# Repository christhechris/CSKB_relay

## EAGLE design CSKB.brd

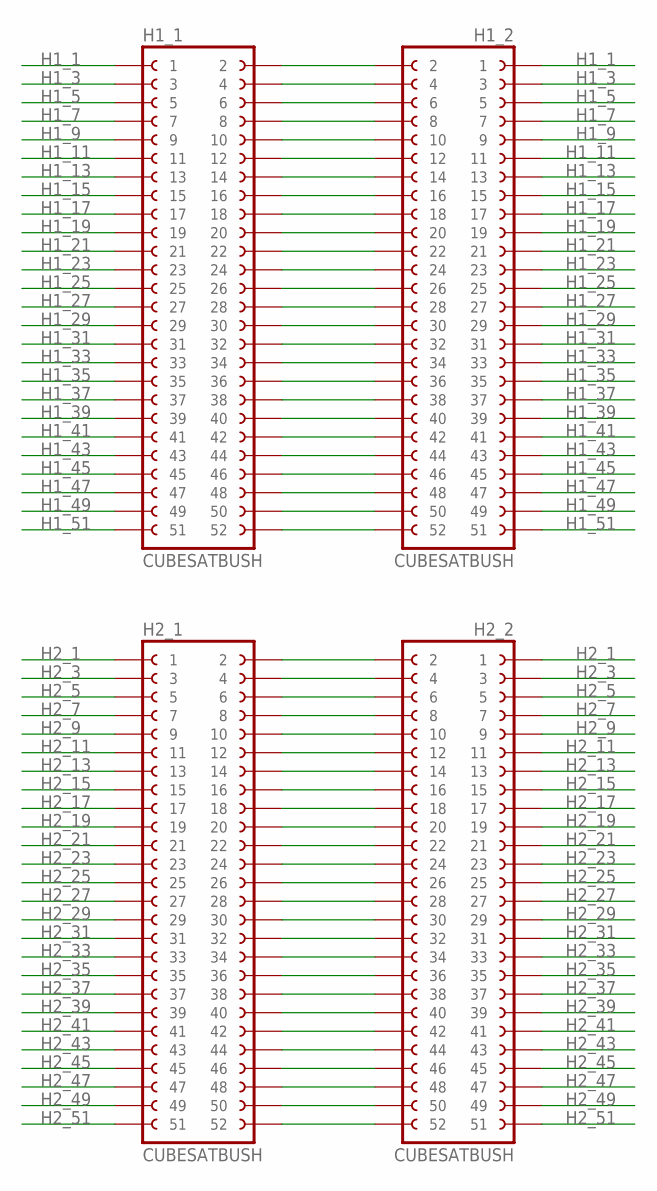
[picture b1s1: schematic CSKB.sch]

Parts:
H1_1, H1_2, H2_1, H2_2: CUBESATBUSH; 2X26HEADER

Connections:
H1_1: H1_1.1, H1_2.1
H1_3: H1_1.3, H1_2.3
H1_5: H1_1.5, H1_2.5
H1_7: H1_1.7, H1_2.7
H1_9: H1_1.9, H1_2.9
H1_11: H1_1.11, H1_2.11
H1_13: H1_1.13, H1_2.13
H1_15: H1_1.15, H1_2.15
H1_17: H1_1.17, H1_2.17
H1_19: H1_1.19, H1_2.19
H1_21: H1_1.21, H1_2.21
H1_23: H1_1.23, H1_2.23
H1_25: H1_1.25, H1_2.25
H1_27: H1_1.27, H1_2.27
H1_29: H1_1.29, H1_2.29
H1_31: H1_1.31, H1_2.31
H1_33: H1_1.33, H1_2.33
H1_35: H1_1.35, H1_2.35
H1_37: H1_1.37, H1_2.37
H1_39: H1_1.39, H1_2.39
H1_41: H1_1.41, H1_2.41
H1_43: H1_1.43, H1_2.43
H1_45: H1_1.45, H1_2.45
H1_47: H1_1.47, H1_2.47
H1_49: H1_1.49, H1_2.49
H1_51: H1_1.51, H1_2.51
H2_1: H2_1.1, H2_2.1
H2_3: H2_1.3, H2_2.3
H2_5: H2_1.5, H2_2.5
H2_7: H2_1.7, H2_2.7
H2_9: H2_1.9, H2_2.9
H2_11: H2_1.11, H2_2.11
H2_13: H2_1.13, H2_2.13
H2_15: H2_1.15, H2_2.15
H2_17: H2_1.17, H2_2.17
H2_19: H2_1.19, H2_2.19
H2_21: H2_1.21, H2_2.21
H2_23: H2_1.23, H2_2.23
H2_25: H2_1.25, H2_2.25
H2_27: H2_1.27, H2_2.27
H2_29: H2_1.29, H2_2.29
H2_31: H2_1.31, H2_2.31
H2_33: H2_1.33, H2_2.33
H2_35: H2_1.35, H2_2.35
H2_37: H2_1.37, H2_2.37
H2_39: H2_1.39, H2_2.39
H2_41: H2_1.41, H2_2.41
H2_43: H2_1.43, H2_2.43
H2_45: H2_1.45, H2_2.45
H2_47: H2_1.47, H2_2.47
H2_49: H2_1.49, H2_2.49
H2_51: H2_1.51, H2_2.51
unnamed: H1_1.2, H1_2.2
unnamed: H1_1.4, H1_2.4
unnamed: H1_1.6, H1_2.6
unnamed: H1_1.8, H1_2.8
unnamed: H1_1.12, H1_2.12
unnamed: H1_1.10, H1_2.10
unnamed: H1_1.14, H1_2.14
unnamed: H1_1.16, H1_2.16
unnamed: H1_1.18, H1_2.18
unnamed: H1_1.20, H1_2.20
unnamed: H1_1.22, H1_2.22
unnamed: H1_1.24, H1_2.24
unnamed: H1_1.26, H1_2.26
unnamed: H1_1.28, H1_2.28
unnamed: H1_1.30, H1_2.30
unnamed: H1_1.32, H1_2.32
unnamed: H1_1.34, H1_2.34
unnamed: H1_1.36, H1_2.36
unnamed: H1_1.38, H1_2.38
unnamed: H1_1.42, H1_2.42
unnamed: H1_1.40, H1_2.40
unnamed: H1_1.44, H1_2.44
unnamed: H1_1.46, H1_2.46
unnamed: H1_1.48, H1_2.48
unnamed: H1_1.50, H1_2.50
unnamed: H1_1.52, H1_2.52
unnamed: H2_1.2, H2_2.2
unnamed: H2_1.4, H2_2.4
unnamed: H2_1.6, H2_2.6
unnamed: H2_1.8, H2_2.8
unnamed: H2_1.12, H2_2.12
unnamed: H2_1.10, H2_2.10
unnamed: H2_1.14, H2_2.14
unnamed: H2_1.16, H2_2.16
unnamed: H2_1.18, H2_2.18
unnamed: H2_1.20, H2_2.20
unnamed: H2_1.22, H2_2.22
unnamed: H2_1.24, H2_2.24
unnamed: H2_1.26, H2_2.26
unnamed: H2_1.28, H2_2.28
unnamed: H2_1.30, H2_2.30
unnamed: H2_1.32, H2_2.32
unnamed: H2_1.34, H2_2.34
unnamed: H2_1.36, H2_2.36
unnamed: H2_1.38, H2_2.38
unnamed: H2_1.42, H2_2.42
unnamed: H2_1.40, H2_2.40
unnamed: H2_1.44, H2_2.44
unnamed: H2_1.46, H2_2.46
unnamed: H2_1.48, H2_2.48
unnamed: H2_1.50, H2_2.50
unnamed: H2_1.52, H2_2.52

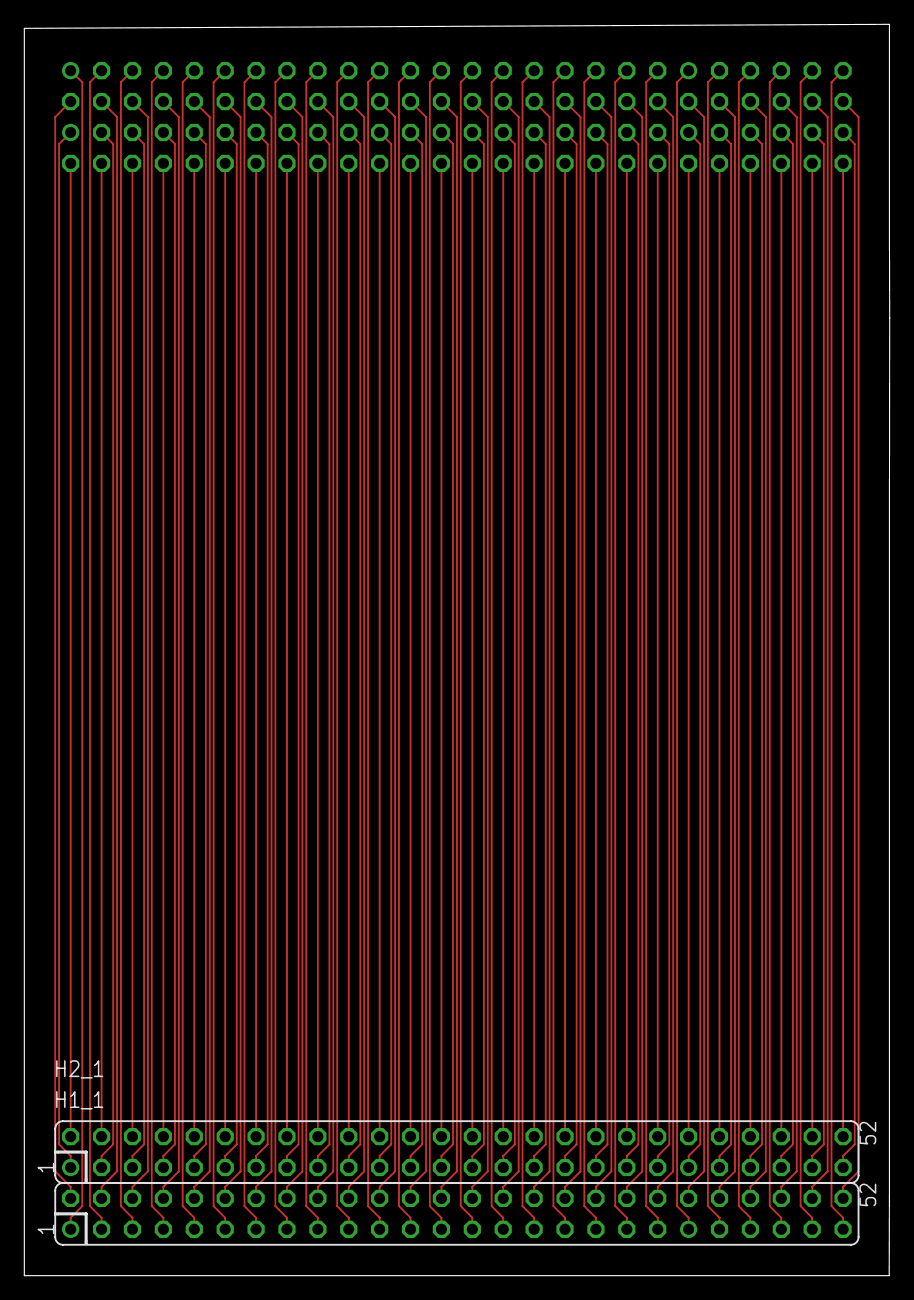
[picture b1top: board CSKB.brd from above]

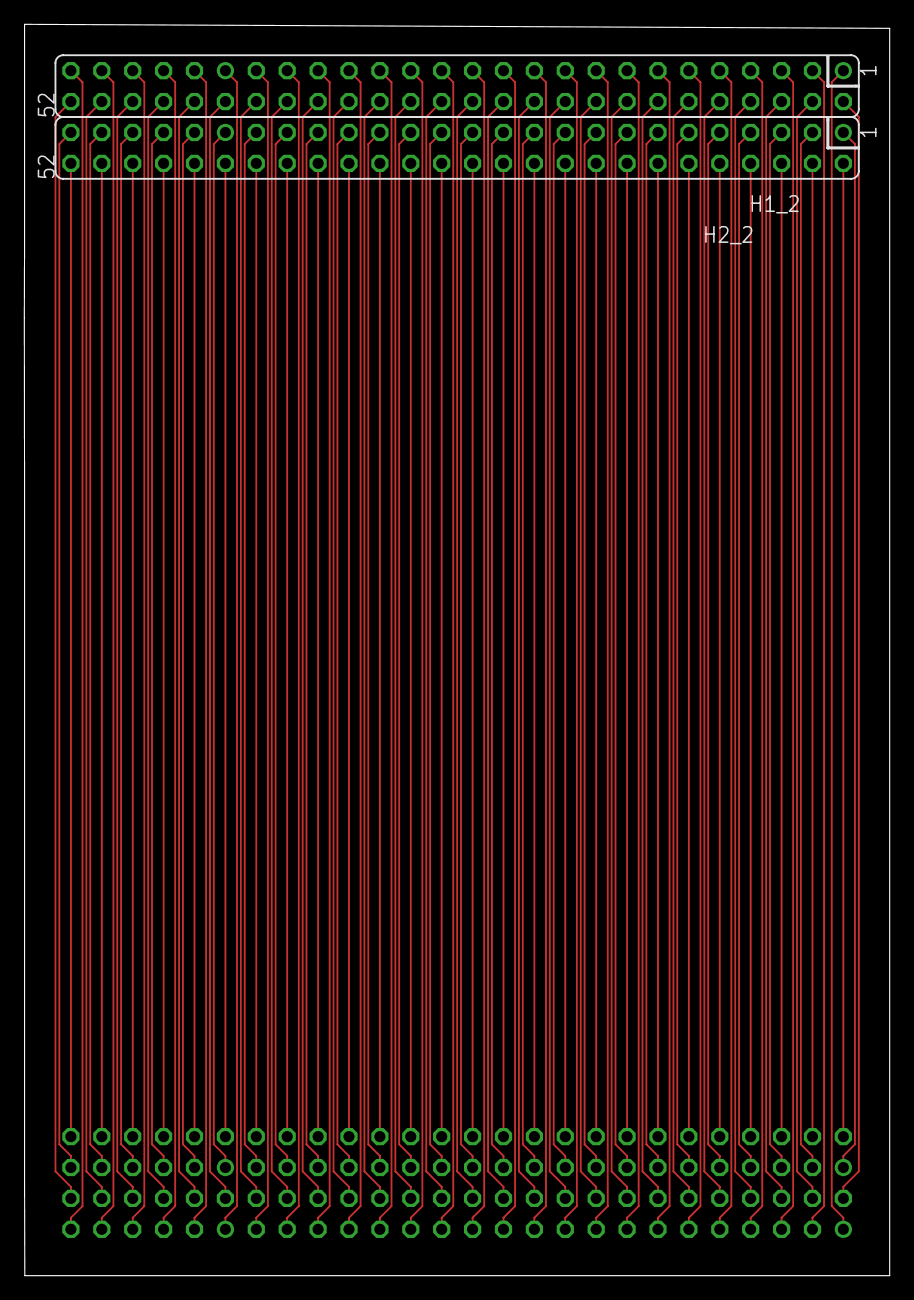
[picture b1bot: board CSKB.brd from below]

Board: 2 copper layers, 71.1 x 102.9 mm, 4 parts (2 on the bottom side), 104 nets.

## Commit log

2019-02-27 init commit
